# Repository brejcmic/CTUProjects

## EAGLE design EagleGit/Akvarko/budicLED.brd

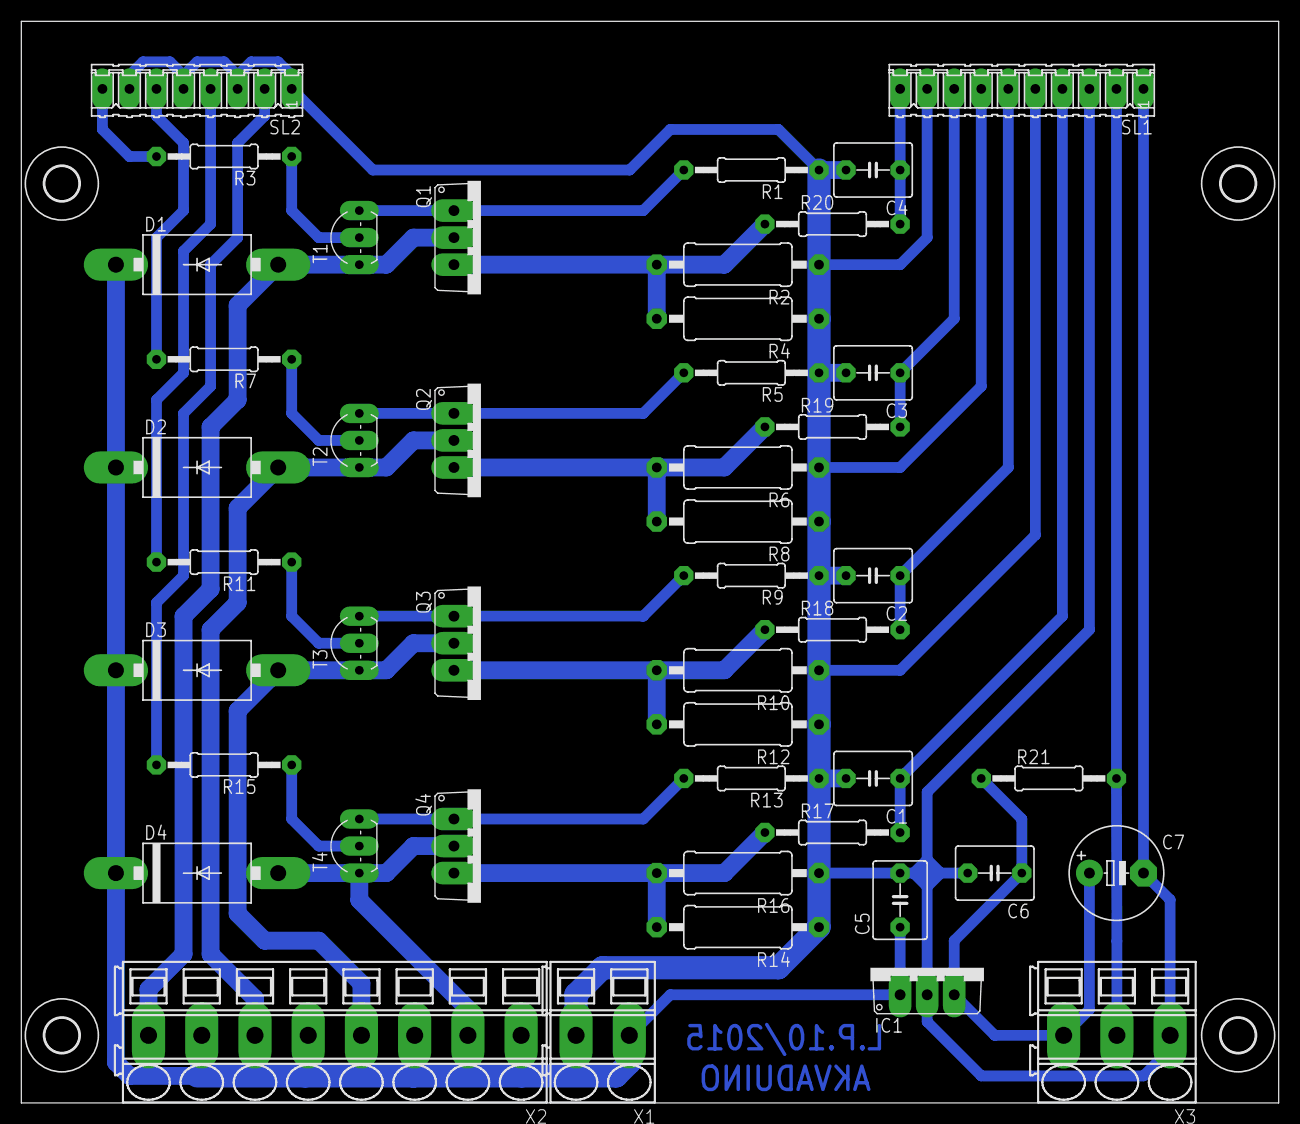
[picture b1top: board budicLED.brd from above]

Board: 2 copper layers, 118.1 x 101.6 mm, 50 parts (0 on the bottom side), 28 nets.

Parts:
C1, C2, C3, C4, C5: 330n; C050-050X075
C6: 100n; C050-050X075
C7: 10u; E5-8,5
D1, D2, D3, D4: DO201-15
IC1: 7805TV; TO220V
Q1, Q2, Q3, Q4: BD243C; TO220V
R1, R5, R9, R13: 1k; 0207/12
R2, R4, R6, R8, R10, R12, R14, R16: 1R; 0411/15
R3, R7, R11, R15: 220R; 0207/12
R17, R18, R19, R20, R21: 4k7; 0207/12
SL1: 10P
SL2: 08P
T1, T2, T3, T4: 2N5551; TO92-CBE
U$1, U$2, U$3, U$4: 3,2
X1: SMKDSP_1,5/2
X2: SMKDSP_1,5/8
X3: SMKDSP_1,5/3

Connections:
+12V: C5.1, D1.C, D2.C, D3.C, D4.C, IC1.1, X1.1, X2.1, X2.3, X2.5, X2.7
GND: C1.2, C2.2, C3.2, C4.2, C5.2, C6.2, C7.-, IC1.2, R1.1, R2.1, R4.1, R5.1, R6.1, R8.1, R9.1, R10.1, R12.1, R13.1, R14.1, R16.1, SL1.1, SL1.3, SL1.5, SL1.7, SL1.9, SL2.1, SL2.3, SL2.5, SL2.7, X1.2, X3.1
unnamed: Q1.1, R1.2, T1.E
unnamed: D1.A, Q1.2, T1.C, X2.8
unnamed: R3.1, T1.B
unnamed: D2.A, Q2.2, T2.C, X2.6
unnamed: D3.A, Q3.2, T3.C, X2.4
unnamed: Q2.1, R5.2, T2.E
unnamed: D4.A, Q4.2, T4.C, X2.2
unnamed: R7.1, T2.B
unnamed: Q3.1, R9.2, T3.E
unnamed: R3.2, SL2.8
unnamed: R11.1, T3.B
unnamed: Q4.1, R13.2, T4.E
unnamed: R7.2, SL2.6
unnamed: R15.1, T4.B
unnamed: R11.2, SL2.4
unnamed: R15.2, SL2.2
unnamed: C4.1, R20.2, SL1.10
unnamed: C2.1, R18.2, SL1.6
unnamed: C3.1, R19.2, SL1.8
unnamed: C1.1, R17.2, SL1.4
unnamed: R21.2, SL1.2, X3.2
unnamed: C6.1, C7.+, IC1.3, R21.1, X3.3
SENS1: Q4.3, R14.2, R16.2, R17.1
SENS2: Q3.3, R10.2, R12.2, R18.1
SENS3: Q2.3, R6.2, R8.2, R19.1
SENS4: Q1.3, R2.2, R4.2, R20.1

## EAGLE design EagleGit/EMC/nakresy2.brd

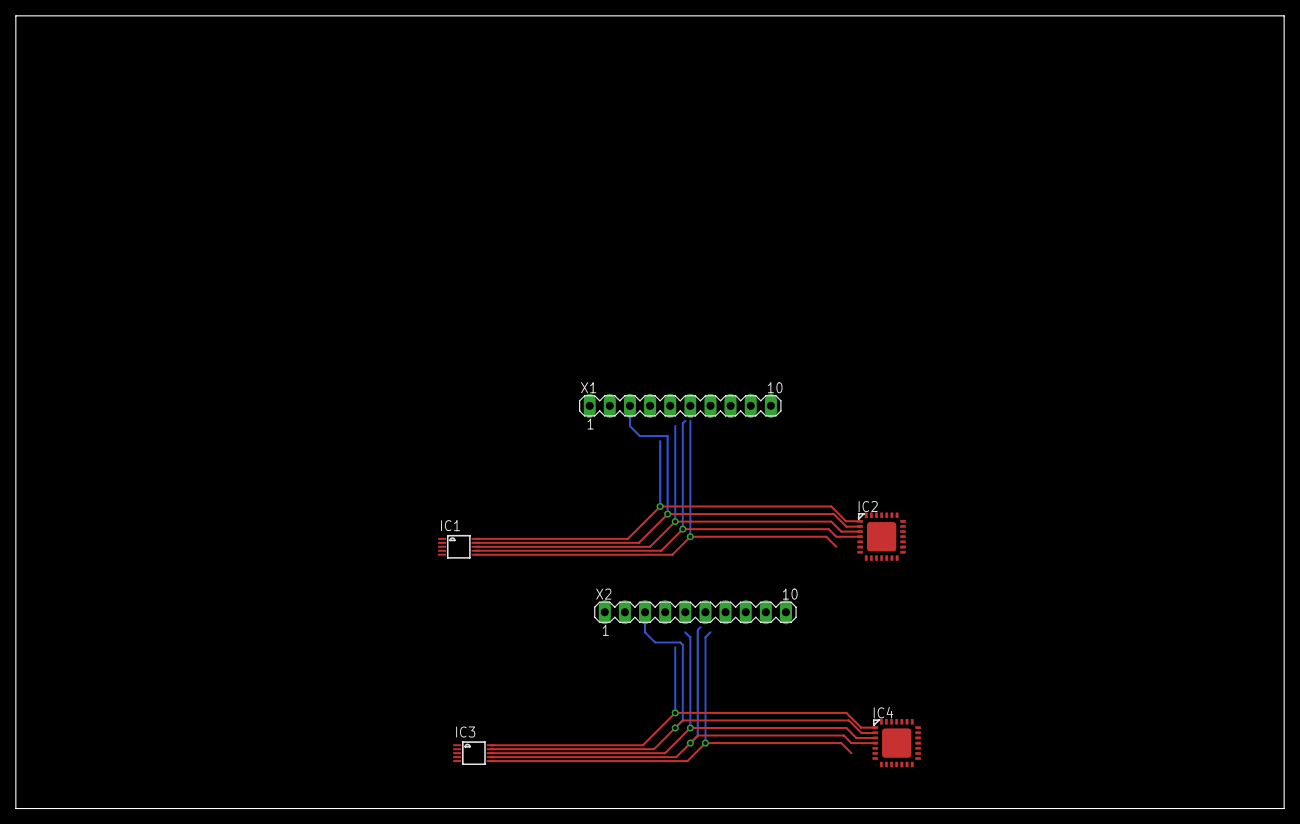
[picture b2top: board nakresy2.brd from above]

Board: 4 copper layers, 160.0 x 100.0 mm, 6 parts (0 on the bottom side), 12 nets.

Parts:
IC1, IC3: AD7992; MSOP10
IC2, IC4: PIC24FJ32GA002_QFN; QFN28-ML_6X6MM
X1, X2: MA10-1

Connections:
unnamed: IC1.10, IC2.1, X1.1
unnamed: IC1.9, IC2.2, X1.3
unnamed: IC1.8, IC2.3, X1.5
unnamed: IC1.7, IC2.4, X1.7
unnamed: IC1.6, IC2.5, X1.9
unnamed: IC3.10, IC4.1, X2.1
unnamed: IC3.9, IC4.2, X2.3
unnamed: IC3.8, IC4.3, X2.5
unnamed: IC3.7, IC4.4, X2.7
unnamed: IC3.6, IC4.5, X2.9
VDD: IC1.3, IC2.10, IC2.25
VDD1: IC3.3, IC4.10, IC4.25

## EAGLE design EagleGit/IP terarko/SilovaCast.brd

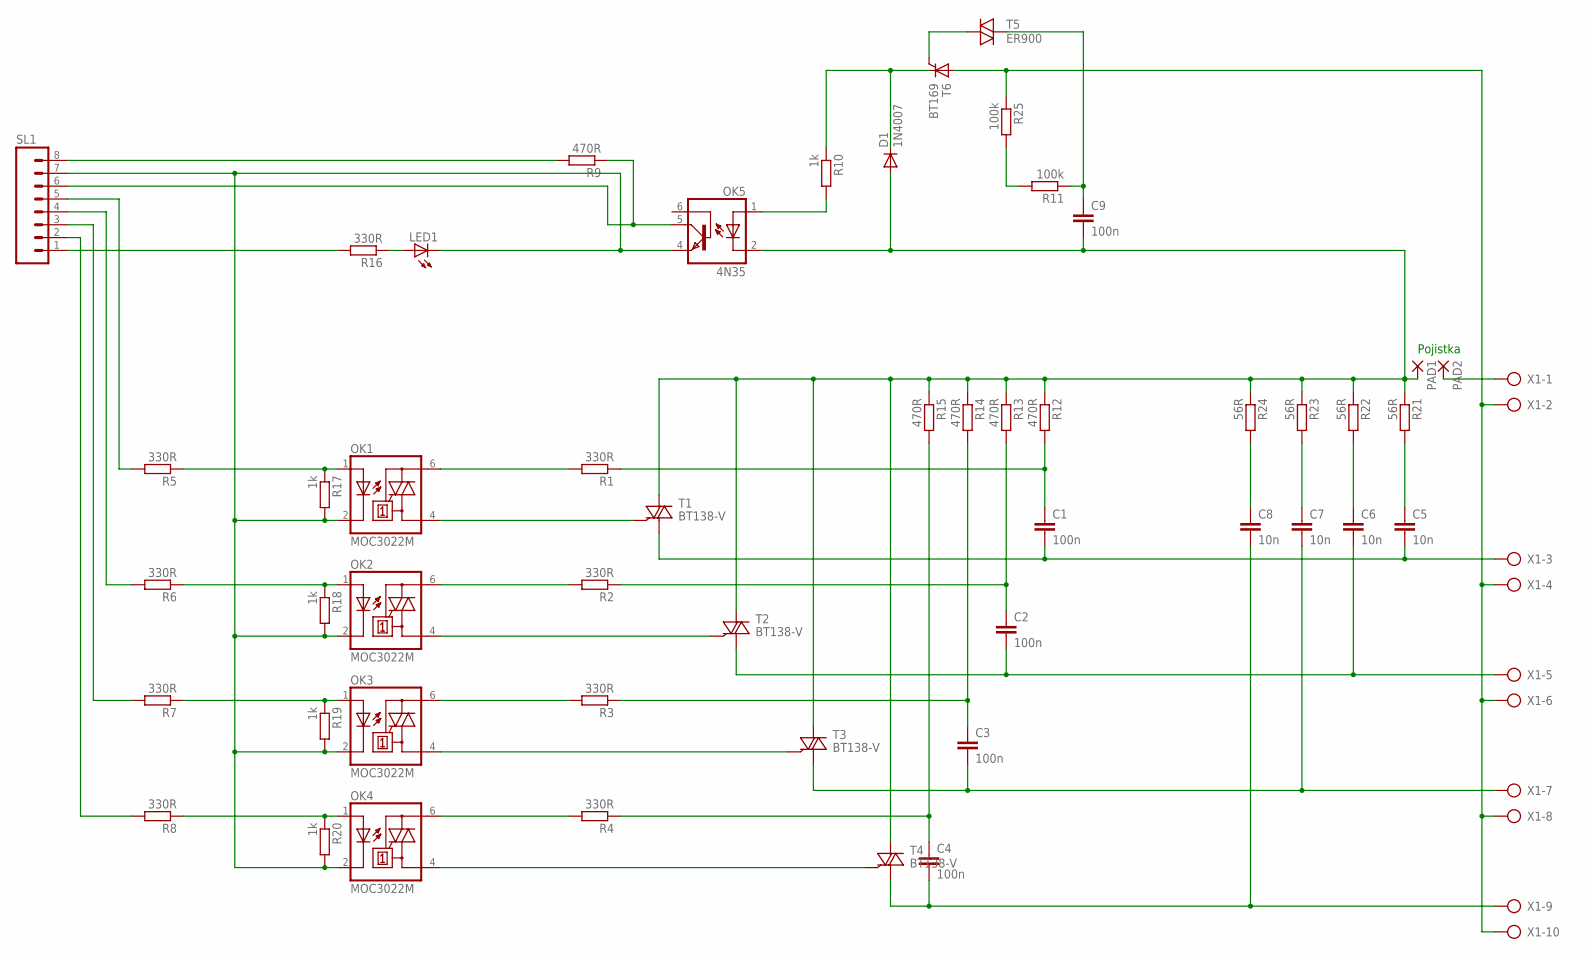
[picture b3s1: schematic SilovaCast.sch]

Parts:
C1, C2, C3, C4, C9: 100n; C7.5B6
C5, C6, C7, C8: 10n; C7.5B6
D1: 1N4007; DO41-10
LED1: LED5MM
OK1, OK2, OK3, OK4: MOC3022M; DIL06
OK5: 4N35; DIL06
PAD1, PAD2: 3,17/1,3
R1, R2, R3, R4, R16: 330R; 0207/12
R5, R6, R7, R8: 330R; R0805
R9, R12, R13, R14, R15: 470R; 0207/12
R10: 1k; 0207/12
R11, R25: 100k; 0207/12
R17, R18, R19, R20: 1k; R0805
R21, R22, R23, R24: 56R; 0411/15
SL1: M08; 08P
T1, T2, T3, T4: BT138-V; TO220BV
T5: ER900
T6: BT169; TO92-2
X1: AK300/10

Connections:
L: C9.2, D1.A, OK5.2 (C), PAD1.1, R12.1, R13.1, R14.1, R15.1, R21.1, R22.1, R23.1, R24.1, T1.T2 (A2), T2.T2 (A2), T3.T2 (A2), T4.T2 (A2)
unnamed: C3.2, C7.2, T3.T1 (A1), X1.7
unnamed: C4.2, C8.2, T4.T1 (A1), X1.9
unnamed: C2.2, C6.2, T2.T1 (A1), X1.5
unnamed: OK3.4 (A1), T3.G
unnamed: OK4.4 (A1), T4.G
unnamed: OK2.4 (A1), T2.G
unnamed: OK1.4 (A1), T1.G
unnamed: C1.2, C5.2, T1.T1 (A1), X1.3
unnamed: OK1.6 (A2), R1.2
unnamed: OK2.6 (A2), R2.2
unnamed: OK3.6 (A2), R3.2
unnamed: OK4.6 (A2), R4.2
unnamed: T5.1, T6.G
unnamed: C9.1, R11.1, T5.2
unnamed: OK5.1 (A), R10.2
unnamed: PAD2.1, X1.1
unnamed: R9.2, SL1.8
unnamed: D1.C, R10.1, T6.C
unnamed: R11.2, R25.2
unnamed: C2.1, R2.1, R13.2
unnamed: C3.1, R3.1, R14.2
unnamed: OK5.5 (COL), R9.1, SL1.6
unnamed: LED1.K (C), OK1.2 (C), OK2.2 (C), OK3.2 (C), OK4.2 (C), OK5.4 (EMI), R17.2, R18.2, R19.2, R20.2, SL1.7
unnamed: OK1.1 (A), R5.1, R17.1
unnamed: OK2.1 (A), R6.1, R18.1
unnamed: OK3.1 (A), R7.1, R19.1
unnamed: OK4.1 (A), R8.1, R20.1
unnamed: R5.2, SL1.5
unnamed: R6.2, SL1.4
unnamed: R7.2, SL1.3
unnamed: R8.2, SL1.2
unnamed: C4.1, R4.1, R15.2
unnamed: C1.1, R1.1, R12.2
unnamed: R16.2, SL1.1
unnamed: LED1.A, R16.1
unnamed: C5.1, R21.2
unnamed: C6.1, R22.2
unnamed: C7.1, R23.2
unnamed: C8.1, R24.2
N_PEN: R25.1, T6.A, X1.2, X1.4, X1.6, X1.8, X1.10

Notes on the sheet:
Pojistka

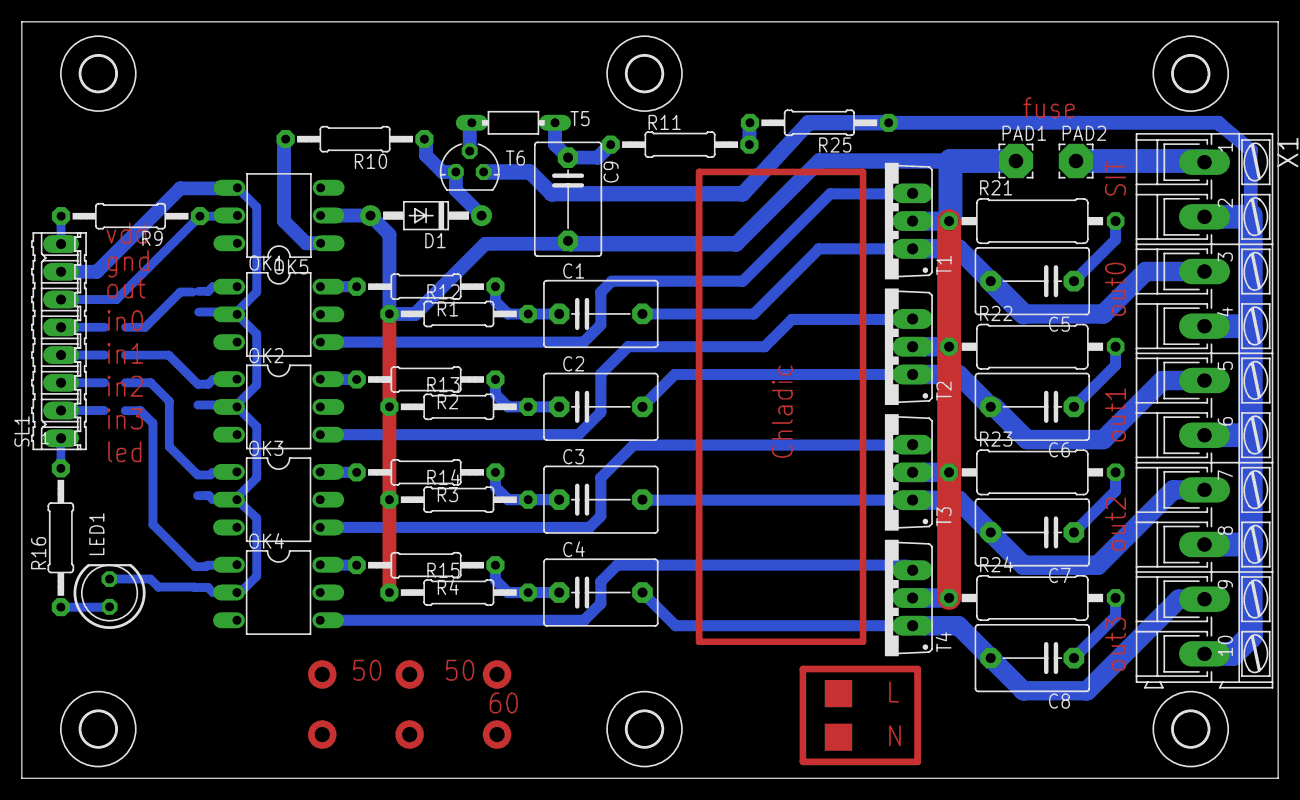
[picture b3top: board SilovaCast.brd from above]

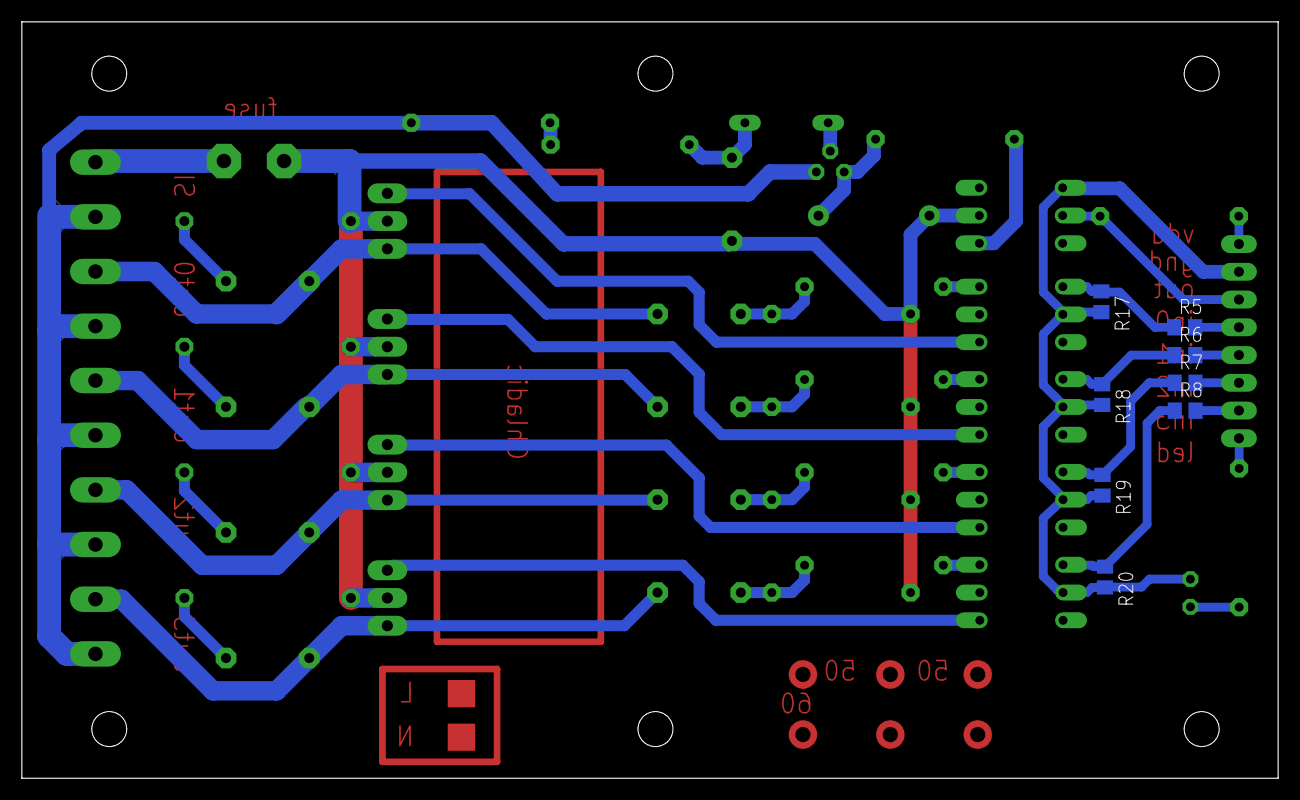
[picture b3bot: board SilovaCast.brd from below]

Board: 2 copper layers, 115.0 x 69.2 mm, 57 parts (8 on the bottom side), 41 nets.

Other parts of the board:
U$1, U$2, U$3, U$4, U$5, U$6: 3,2

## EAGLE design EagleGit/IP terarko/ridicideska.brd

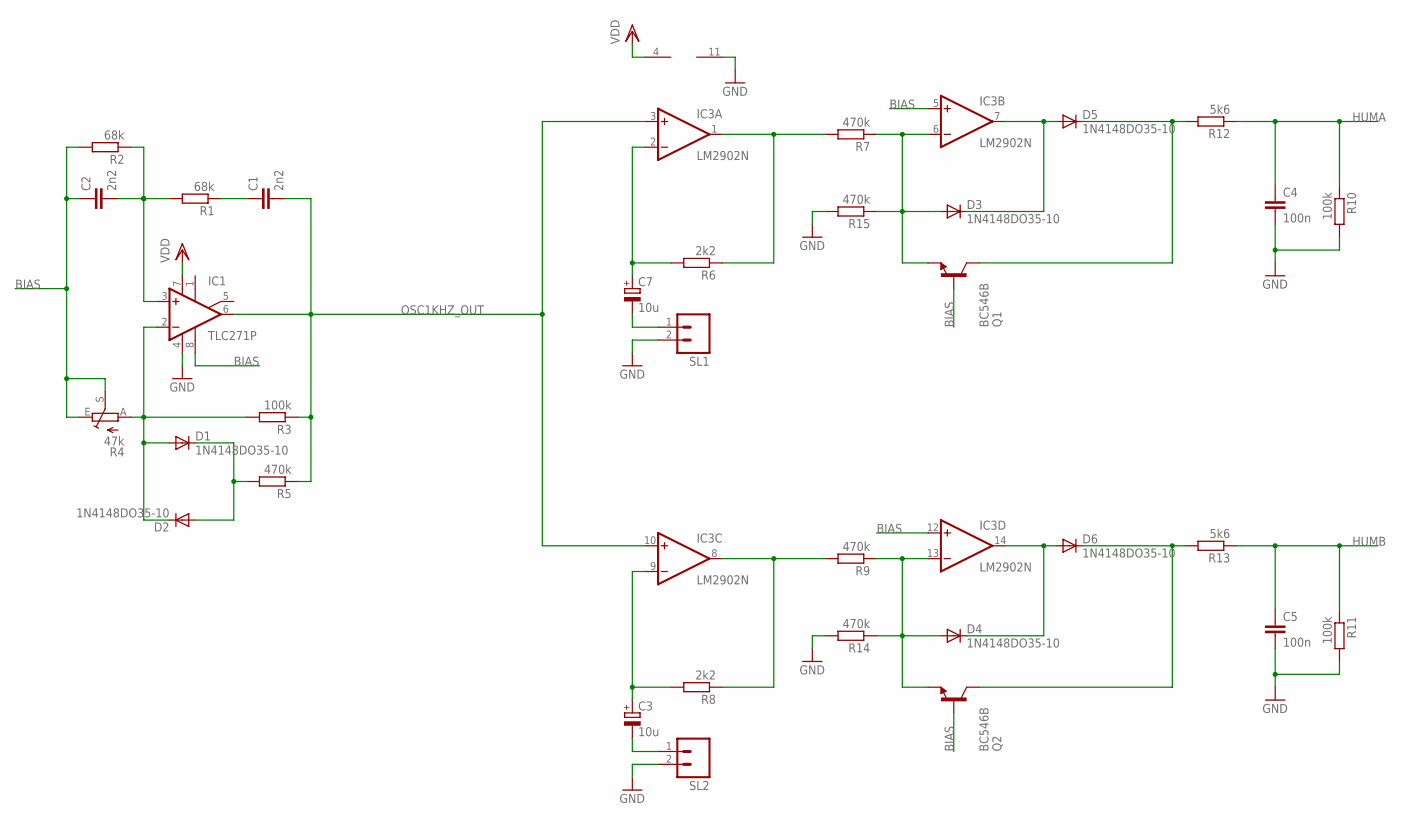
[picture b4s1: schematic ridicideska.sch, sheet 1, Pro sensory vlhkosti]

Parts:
C1, C2: 2n2; C0805
C3, C7: 10u; E5-13
C4, C5: 100n; C0805
D1, D2, D3, D4, D5, D6: 1N4148DO35-10; DO35-10
IC1: TLC271P; DIL08
IC3: LM2902N; DIL14
Q1, Q2: BC546B; TO92-EBC
R1, R2: 68k; R0805
R3, R10, R11: 100k; R0805
R4: 47k; CA6V
R5, R7, R9, R14, R15: 470k; R0805
R6, R8: 2k2; R0805
R12, R13: 5k6; R0805
SL1, SL2: M02; 02P

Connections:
BIAS: C2.1, IC1.8 (OPT), IC3.5 (+IN), IC3.12 (+IN), Q1.B, Q2.B, R2.2, R4.E, R4.S; also elsewhere on the board
GND: C4.2, C5.2, IC1.4 (V-), IC3.11 (V-), R10.2, R11.2, R14.2, R15.2, SL1.2, SL2.2; also elsewhere on the board
HUMA: C4.1, R10.1, R12.1; also elsewhere on the board
HUMB: C5.1, R11.1, R13.1; also elsewhere on the board
unnamed: IC3.1 (OUT), R6.1, R7.2
unnamed: C1.1, R1.1
unnamed: C2.2, IC1.3 (+IN), R1.2, R2.1
unnamed: C7.+, IC3.2 (-IN), R6.2
unnamed: D1.A, D2.C, IC1.2 (-IN), R3.2, R4.A
unnamed: C7.-, SL1.1
unnamed: D1.C, D2.A, R5.2
unnamed: D3.A, IC3.6 (-IN), Q1.E, R7.1, R15.1
unnamed: D5.C, Q1.C, R12.2
unnamed: D3.C, D5.A, IC3.7 (OUT)
unnamed: IC3.8 (OUT), R8.1, R9.2
unnamed: C3.+, IC3.9 (-IN), R8.2
unnamed: C3.-, SL2.1
unnamed: D4.A, IC3.13 (-IN), Q2.E, R9.1, R14.1
unnamed: D4.C, D6.A, IC3.14 (OUT)
unnamed: D6.C, Q2.C, R13.2
OSC1KHZ_OUT: C1.2, IC1.6 (OUT), IC3.3 (+IN), IC3.10 (+IN), R3.1, R5.1
VDD: IC1.7 (V+), IC3.4 (V+); also elsewhere on the board

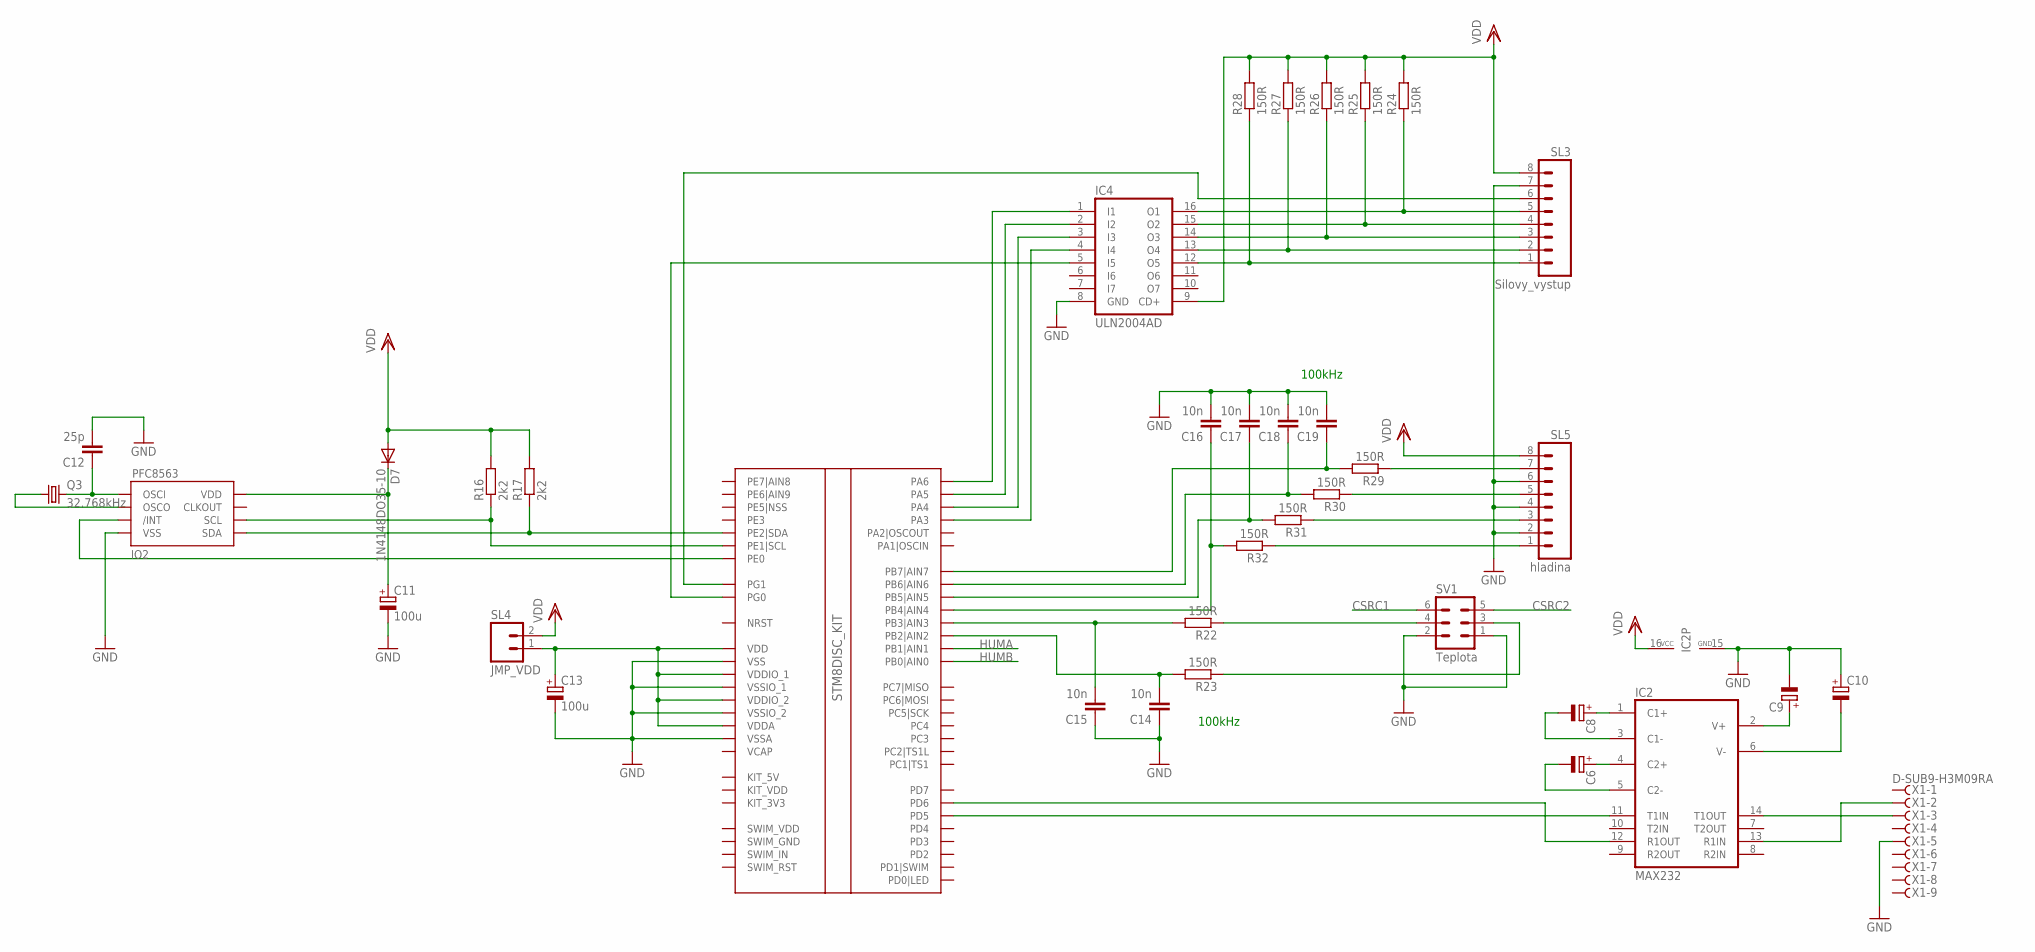
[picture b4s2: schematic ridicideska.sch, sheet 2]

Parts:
C6, C8, C9, C10: CPOL-EUE5-10.5; E5-10,5
C11, C13: 100u; E5-10,5
C12: 25p; C0805
C14, C15, C16, C17, C18, C19: 10n; C0805
D7: 1N4148DO35-10; DO35-10
IC2: MAX232; DIL16
IC4: ULN2004AD; SO16
IO1: STM8_KIT; STM8SDISCOVERY
IO2: PFC8563; SO08
Q3: 32.768kHz; HC49U70
R16, R17: 2k2; 0207/12
R22, R23, R29, R30, R31, R32: 150R; R0805
R24, R25, R26, R27, R28: 150R; 0207/12
SL3: Silovy_vystup; 08P
SL4: JMP_VDD; 02P
SL5: hladina; 08P
SV1: Teplota; MA03-2
X1: D-SUB9-H3M09RA; H3M09RA

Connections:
CSRC1: SV1.6; also elsewhere on the board
CSRC2: SV1.5; also elsewhere on the board
GND: C9.-, C10.+, C11.-, C12.2, C13.-, C14.1, C15.1, C16.2, C17.2, C18.2, C19.2, IC2.15 (GND), IC4.8 (GND), IO1.VSS, IO1.VSSA, IO1.VSSIO_1, IO1.VSSIO_2, IO2.4 (VSS), SL3.7, SL5.2, SL5.4, SL5.6, SV1.1, SV1.2, X1.5; also elsewhere on the board
HUMA: IO1.PB1 (PB1|AIN1); also elsewhere on the board
HUMB: IO1.PB0 (PB0|AIN0); also elsewhere on the board
unnamed: IC2.11 (T1IN), IO1.PD5
unnamed: IC2.12 (R1OUT), IO1.PD6
unnamed: IC2.14 (T1OUT), X1.3
unnamed: IC2.13 (R1IN), X1.2
unnamed: C9.+, IC2.2 (V+)
unnamed: C10.-, IC2.6 (V-)
unnamed: IO1.PE2 (PE2|SDA), IO2.5 (SDA), R17.1
unnamed: C8.-, IC2.3 (C1-)
unnamed: C8.+, IC2.1 (C1+)
unnamed: C6.+, IC2.4 (C2+)
unnamed: C6.-, IC2.5 (C2-)
unnamed: IO1.PE1 (PE1|SCL), IO2.6 (SCL), R16.1
unnamed: C11.+, D7.C, IO2.8 (VDD)
unnamed: IO1.PE0, IO2.3 (/INT)
unnamed: IC4.1 (I1), IO1.PA6
unnamed: IC4.2 (I2), IO1.PA5
unnamed: IC4.3 (I3), IO1.PA4
unnamed: IC4.4 (I4), IO1.PA3
unnamed: IC4.5 (I5), IO1.PG0
unnamed: IO1.PG1, SL3.6
unnamed: C15.2, IO1.PB3 (PB3|AIN3), R22.2
unnamed: R23.1, SV1.3
unnamed: C12.1, IO2.1 (OSCI), Q3.2
unnamed: IO2.2 (OSCO), Q3.1
unnamed: C13.+, IO1.VDD, IO1.VDDA, IO1.VDDIO_1, IO1.VDDIO_2, SL4.1
unnamed: R22.1, SV1.4
unnamed: C14.2, IO1.PB2 (PB2|AIN2), R23.2
unnamed: IC4.16 (O1), R24.1, SL3.5
unnamed: IC4.15 (O2), R25.1, SL3.4
unnamed: IC4.14 (O3), R26.1, SL3.3
unnamed: IC4.13 (O4), R27.1, SL3.2
unnamed: IC4.12 (O5), R28.1, SL3.1
unnamed: C16.1, IO1.PB4 (PB4|AIN4), R32.2
unnamed: C17.1, IO1.PB5 (PB5|AIN5), R31.2
unnamed: C18.1, IO1.PB6 (PB6|AIN6), R30.2
unnamed: C19.1, IO1.PB7 (PB7|AIN7), R29.2
unnamed: R29.1, SL5.7
unnamed: R30.1, SL5.5
unnamed: R31.1, SL5.3
unnamed: R32.1, SL5.1
VDD: D7.A, IC2.16 (VCC), IC4.9 (CD+), R16.2, R17.2, R24.2, R25.2, R26.2, R27.2, R28.2, SL3.8, SL4.2, SL5.8; also elsewhere on the board

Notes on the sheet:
100kHz

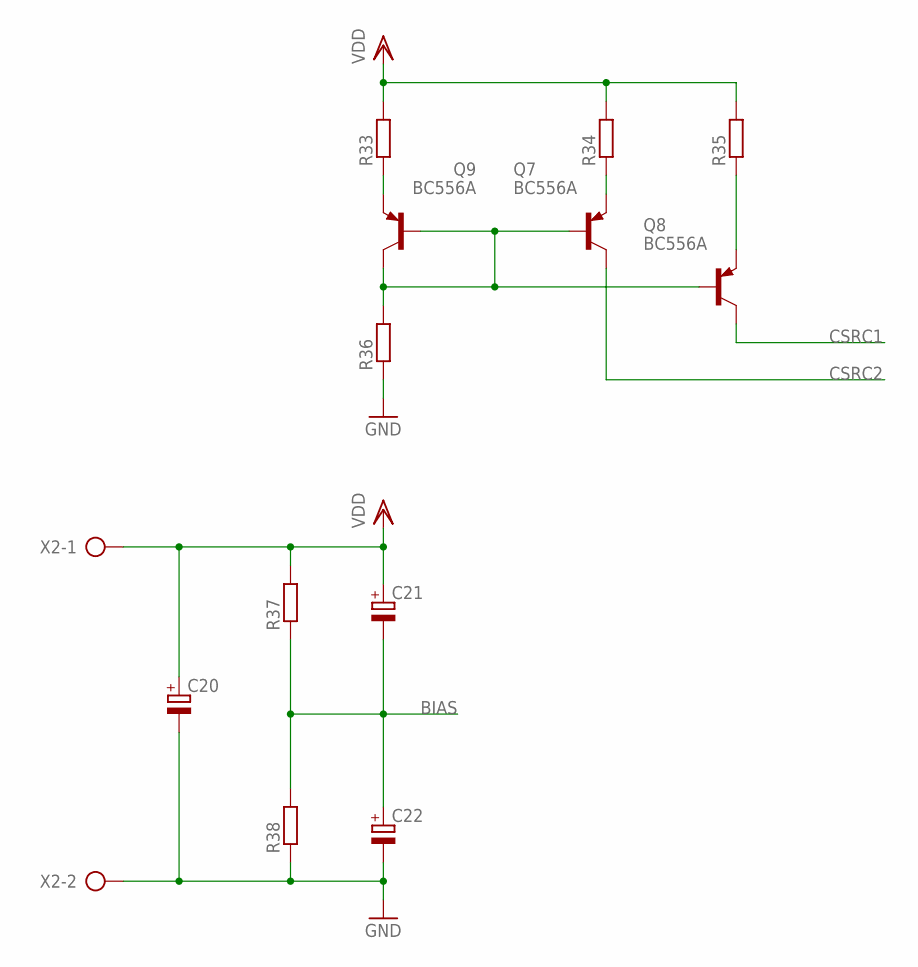
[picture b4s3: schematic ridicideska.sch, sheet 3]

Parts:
C20, C21, C22: CPOL-EUE5-10.5; E5-10,5
Q7, Q8, Q9: BC556A; TO92-EBC
R33, R34, R35, R36: R-EU_R0805; R0805
R37, R38: R-EU_0207/12; 0207/12
X2: AK300/2

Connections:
BIAS: C21.-, C22.+, R37.1, R38.2; also elsewhere on the board
CSRC1: Q8.C; also elsewhere on the board
CSRC2: Q7.C; also elsewhere on the board
GND: C20.-, C22.-, R36.1, R38.1, X2.2; also elsewhere on the board
unnamed: Q7.B, Q8.B, Q9.B, Q9.C, R36.2
unnamed: Q7.E, R34.1
unnamed: Q8.E, R35.1
unnamed: Q9.E, R33.1
VDD: C20.+, C21.+, R33.2, R34.2, R35.2, R37.2, X2.1; also elsewhere on the board

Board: 2 copper layers, 83 parts (0 on the bottom side), 68 nets, no tracks yet.

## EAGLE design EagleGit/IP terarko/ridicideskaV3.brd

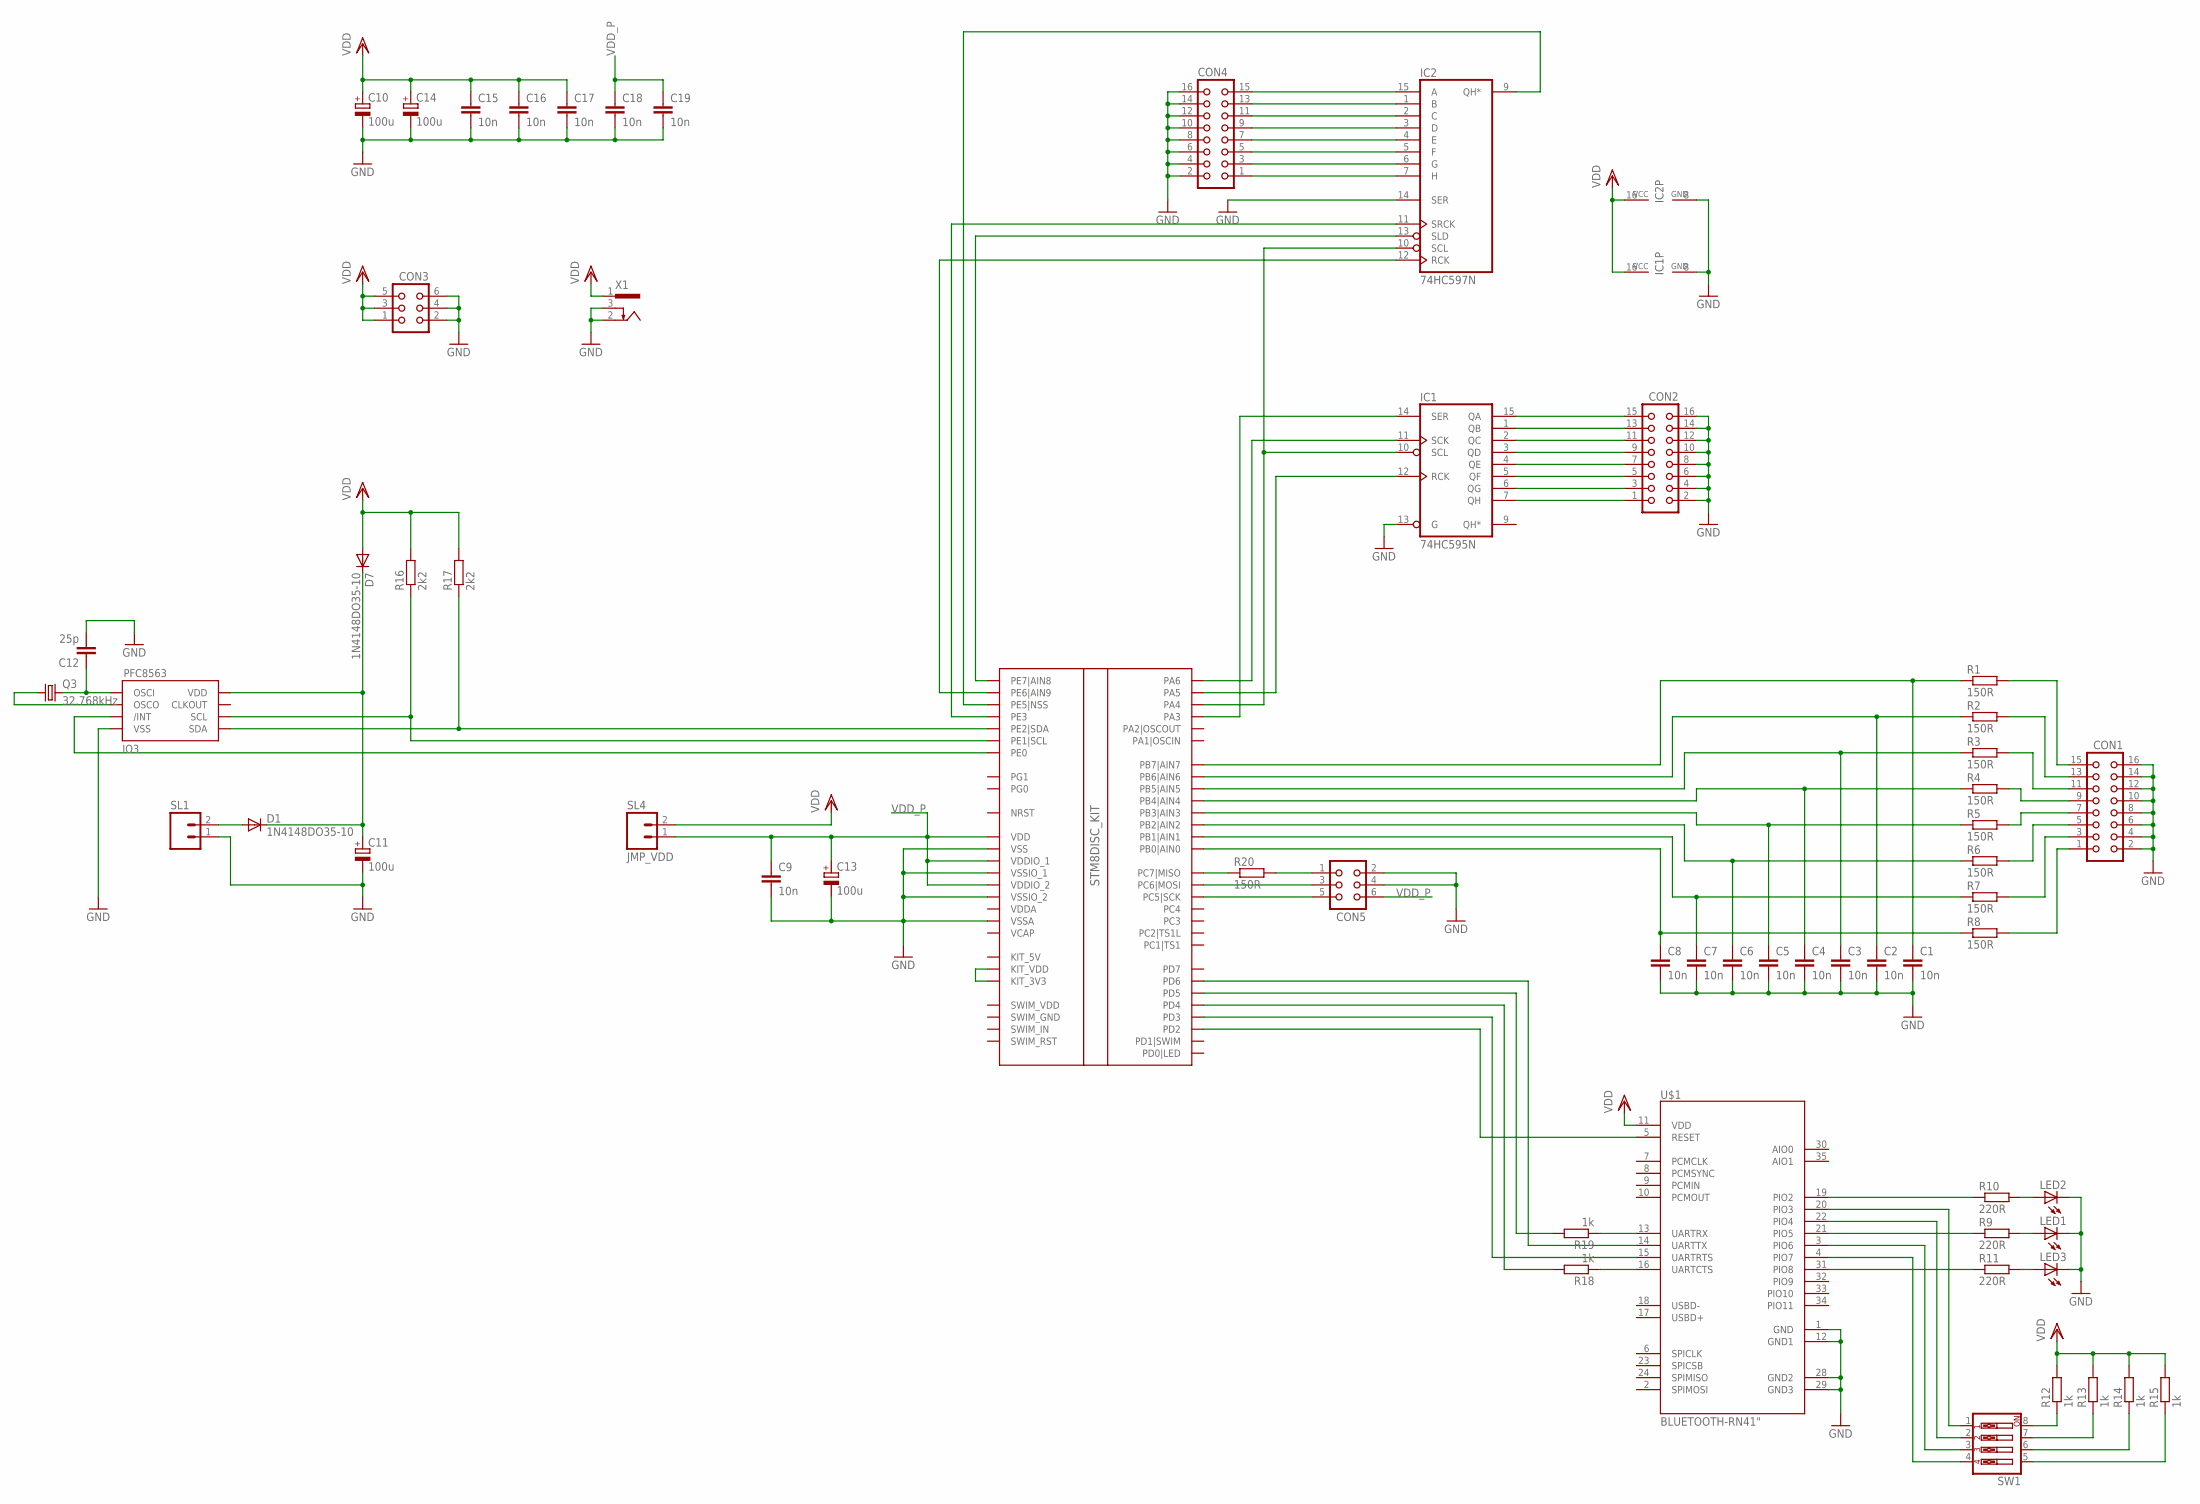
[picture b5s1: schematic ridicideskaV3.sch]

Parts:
C1, C2, C3, C4, C5, C6, C7, C8, C17, C18, C19: 10n; C0805
C9, C15, C16: 10n; C050-045X075
C10, C11, C13, C14: 100u; E5-10,5
C12: 25p; C0603
CON1, CON2, CON4: CON16
CON3, CON5: CON06
D1, D7: 1N4148DO35-10; DO35-10
IC1: 74HC595N; DIL16
IC2: 74HC597N; DIL16
IO1: STM8_KIT; STM8SDISCOVERY
IO3: PFC8563; SO08
LED1, LED2, LED3: LED3MM
Q3: 32.768kHz; TC26V
R1, R2, R3, R4, R5, R6, R7, R8: 150R; 0207/12
R9, R10, R11: 220R; 0207/12
R12, R13, R14, R15, R18, R19: 1k; 0207/12
R16, R17: 2k2; 0207/12
R20: 150R; R0805
SL1: M02; 02P
SL4: JMP_VDD; 02P
SW1: SW_DIP-4; EDG-04
U$1: BLUETOOTH-RN41"; RN41
X1: 733980-62

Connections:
GND: C1.2, C2.2, C3.2, C4.2, C5.2, C6.2, C7.2, C8.2, C9.2, C10.-, C11.-, C12.2, C13.-, C14.-, C15.2, C16.2, C17.2, C18.2, C19.2, CON1.2, CON1.4, CON1.6, CON1.8, CON1.10, CON1.12, CON1.14, CON1.16, CON2.2, CON2.4, CON2.6, CON2.8, CON2.10, CON2.12, CON2.14, CON2.16, CON3.2, CON3.4, CON3.6, CON4.2, CON4.4, CON4.6, CON4.8, CON4.10, CON4.12, CON4.14, CON4.16, CON5.2, CON5.4, IC1.8 (GND), IC1.13 (G), IC2.8 (GND), IC2.14 (SER), IO1.VSS, IO1.VSSA, IO1.VSSIO_1, IO1.VSSIO_2, IO3.4 (VSS), LED1.K (C), LED2.K (C), LED3.K (C), SL1.1, U$1.1 (GND), U$1.12 (GND1), U$1.28 (GND2), U$1.29 (GND3), X1.2, X1.3
unnamed: IC1.14 (SER), IO1.PA3
unnamed: D1.A, SL1.2
unnamed: C8.1, IO1.PB0 (PB0|AIN0), R8.1
unnamed: C7.1, IO1.PB1 (PB1|AIN1), R7.1
unnamed: C6.1, IO1.PB2 (PB2|AIN2), R6.1
unnamed: CON1.15, R1.2
unnamed: CON1.13, R2.2
unnamed: CON1.11, R3.2
unnamed: CON1.9, R4.2
unnamed: CON1.1, R8.2
unnamed: IC1.11 (SCK), IO1.PA6
unnamed: IC1.10 (SCL), IC2.10 (SCL), IO1.PA4
unnamed: IC1.12 (RCK), IO1.PA5
unnamed: CON2.15, IC1.15 (QA)
unnamed: CON2.13, IC1.1 (QB)
unnamed: CON2.11, IC1.2 (QC)
unnamed: CON2.9, IC1.3 (QD)
unnamed: CON2.7, IC1.4 (QE)
unnamed: CON2.5, IC1.5 (QF)
unnamed: CON2.3, IC1.6 (QG)
unnamed: CON2.1, IC1.7 (QH)
unnamed: IC2.13 (SLD), IO1.PE7 (PE7|AIN8)
unnamed: IO1.PE2 (PE2|SDA), IO3.5 (SDA), R17.1
unnamed: IC2.9 (QH*), IO1.PE5 (PE5|NSS)
unnamed: CON1.3, R7.2
unnamed: C5.1, IO1.PB3 (PB3|AIN3), R5.1
unnamed: C1.1, IO1.PB7 (PB7|AIN7), R1.1
unnamed: IO1.PE1 (PE1|SCL), IO3.6 (SCL), R16.1
unnamed: C11.+, D1.C, D7.C, IO3.8 (VDD)
unnamed: IO1.PE0, IO3.3 (/INT)
unnamed: CON4.15, IC2.15 (A)
unnamed: CON4.13, IC2.1 (B)
unnamed: CON4.11, IC2.2 (C)
unnamed: CON4.9, IC2.3 (D)
unnamed: CON4.7, IC2.4 (E)
unnamed: CON4.5, IC2.5 (F)
unnamed: CON4.3, IC2.6 (G)
unnamed: CON4.1, IC2.7 (H)
unnamed: C12.1, IO3.1 (OSCI), Q3.2
unnamed: IO3.2 (OSCO), Q3.1
unnamed: C2.1, IO1.PB6 (PB6|AIN6), R2.1
unnamed: R19.1, U$1.13 (UARTRX)
unnamed: C3.1, IO1.PB5 (PB5|AIN5), R3.1
unnamed: C4.1, IO1.PB4 (PB4|AIN4), R4.1
unnamed: CON1.5, R6.2
unnamed: CON1.7, R5.2
unnamed: IO1.PD5, R19.2
unnamed: IO1.PD6, U$1.14 (UARTTX)
unnamed: LED1.A, R9.2
unnamed: R9.1, U$1.21 (PIO5)
unnamed: R10.1, U$1.19 (PIO2)
unnamed: LED2.A, R10.2
unnamed: SW1.1, U$1.20 (PIO3)
unnamed: SW1.2, U$1.22 (PIO4)
unnamed: SW1.3, U$1.3 (PIO6)
unnamed: SW1.4, U$1.4 (PIO7)
unnamed: R11.1, U$1.31 (PIO8)
unnamed: LED3.A, R11.2
unnamed: R12.1, SW1.8
unnamed: R13.1, SW1.7
unnamed: R14.1, SW1.6
unnamed: R15.1, SW1.5
unnamed: IO1.PD4, R18.2
unnamed: IO1.PD3, U$1.15 (UARTRTS)
unnamed: R18.1, U$1.16 (UARTCTS)
unnamed: IC2.12 (RCK), IO1.PE6 (PE6|AIN9)
unnamed: IC2.11 (SRCK), IO1.PE3
unnamed: IO1.KIT_3V3, IO1.KIT_VDD
unnamed: IO1.PD2, U$1.5 (RESET)
unnamed: IO1.PC7 (PC7|MISO), R20.1
unnamed: CON5.1, R20.2
unnamed: CON5.3, IO1.PC6 (PC6|MOSI)
unnamed: CON5.5, IO1.PC5 (PC5|SCK)
VDD: C10.+, C14.+, C15.1, C16.1, C17.1, CON3.1, CON3.3, CON3.5, D7.A, IC1.16 (VCC), IC2.16 (VCC), R12.2, R13.2, R14.2, R15.2, R16.2, R17.2, SL4.2, U$1.11 (VDD), X1.1
VDD_P: C9.1, C13.+, C18.1, C19.1, CON5.6, IO1.VDD, IO1.VDDIO_1, IO1.VDDIO_2, SL4.1

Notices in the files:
parts and their libraries:
SparkFun-RF: Licensing: Creative Commons ShareAlike 4.0 International - https://creativecommons.org/licenses/by-sa/4.0
